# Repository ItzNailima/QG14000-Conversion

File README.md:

# QG14000-Conversion
 Converting a Quantum Guardian 14000 to use modern hardware

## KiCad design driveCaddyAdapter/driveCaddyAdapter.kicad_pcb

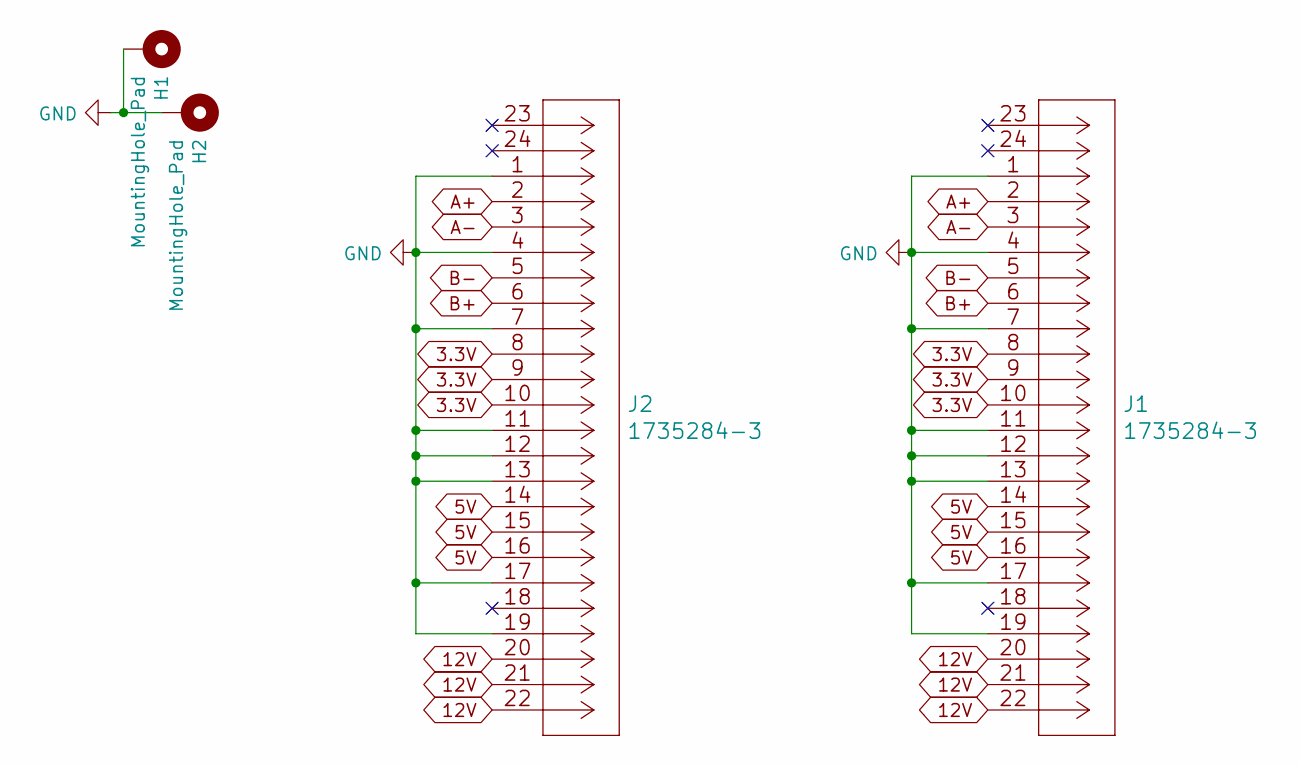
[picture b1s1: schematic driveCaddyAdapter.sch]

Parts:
H1, H2: MountingHole_Pad; TestPoint_Plated_Hole_D2.0mm
J1, J2: 1735284-3

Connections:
3.3V: J1.8, J1.9, J1.10, J2.8, J2.9, J2.10
5V: J1.14, J1.15, J1.16, J2.14, J2.15, J2.16
12V: J1.20, J1.21, J1.22, J2.20, J2.21, J2.22
A+: J1.2, J2.2
A-: J1.3, J2.3
B+: J1.6, J2.6
B-: J1.5, J2.5
GND: H1.1, H2.1, J1.1, J1.4, J1.7, J1.11, J1.12, J1.13, J1.17, J1.19, J2.1, J2.4, J2.7, J2.11, J2.12, J2.13, J2.17, J2.19

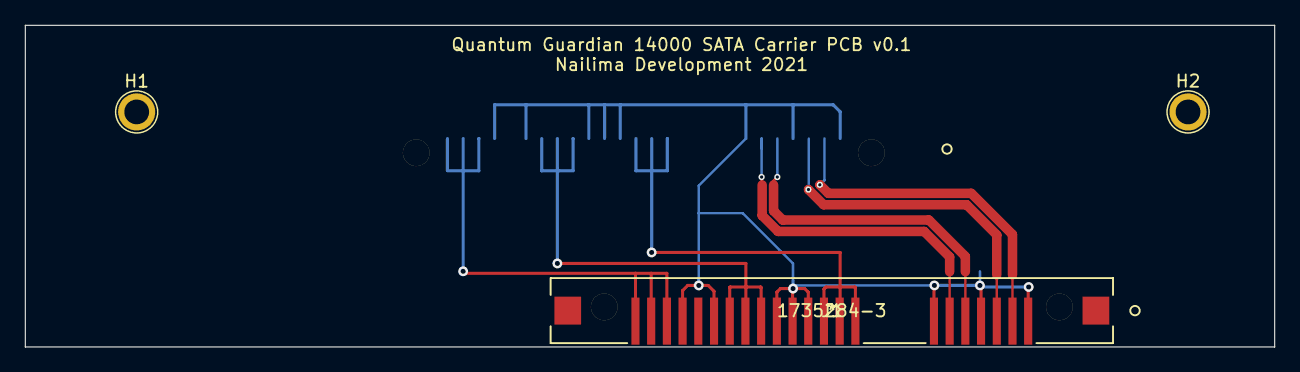
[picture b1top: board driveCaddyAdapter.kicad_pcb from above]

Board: 2 copper layers, 101.0 x 26.0 mm, 4 parts (1 on the bottom side), 8 nets.

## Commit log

2021-04-08 Hotswap Caddy v0.1

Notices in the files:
parts and their libraries:
Copyright 2016 Accelerated Designs. All rights reserved.
